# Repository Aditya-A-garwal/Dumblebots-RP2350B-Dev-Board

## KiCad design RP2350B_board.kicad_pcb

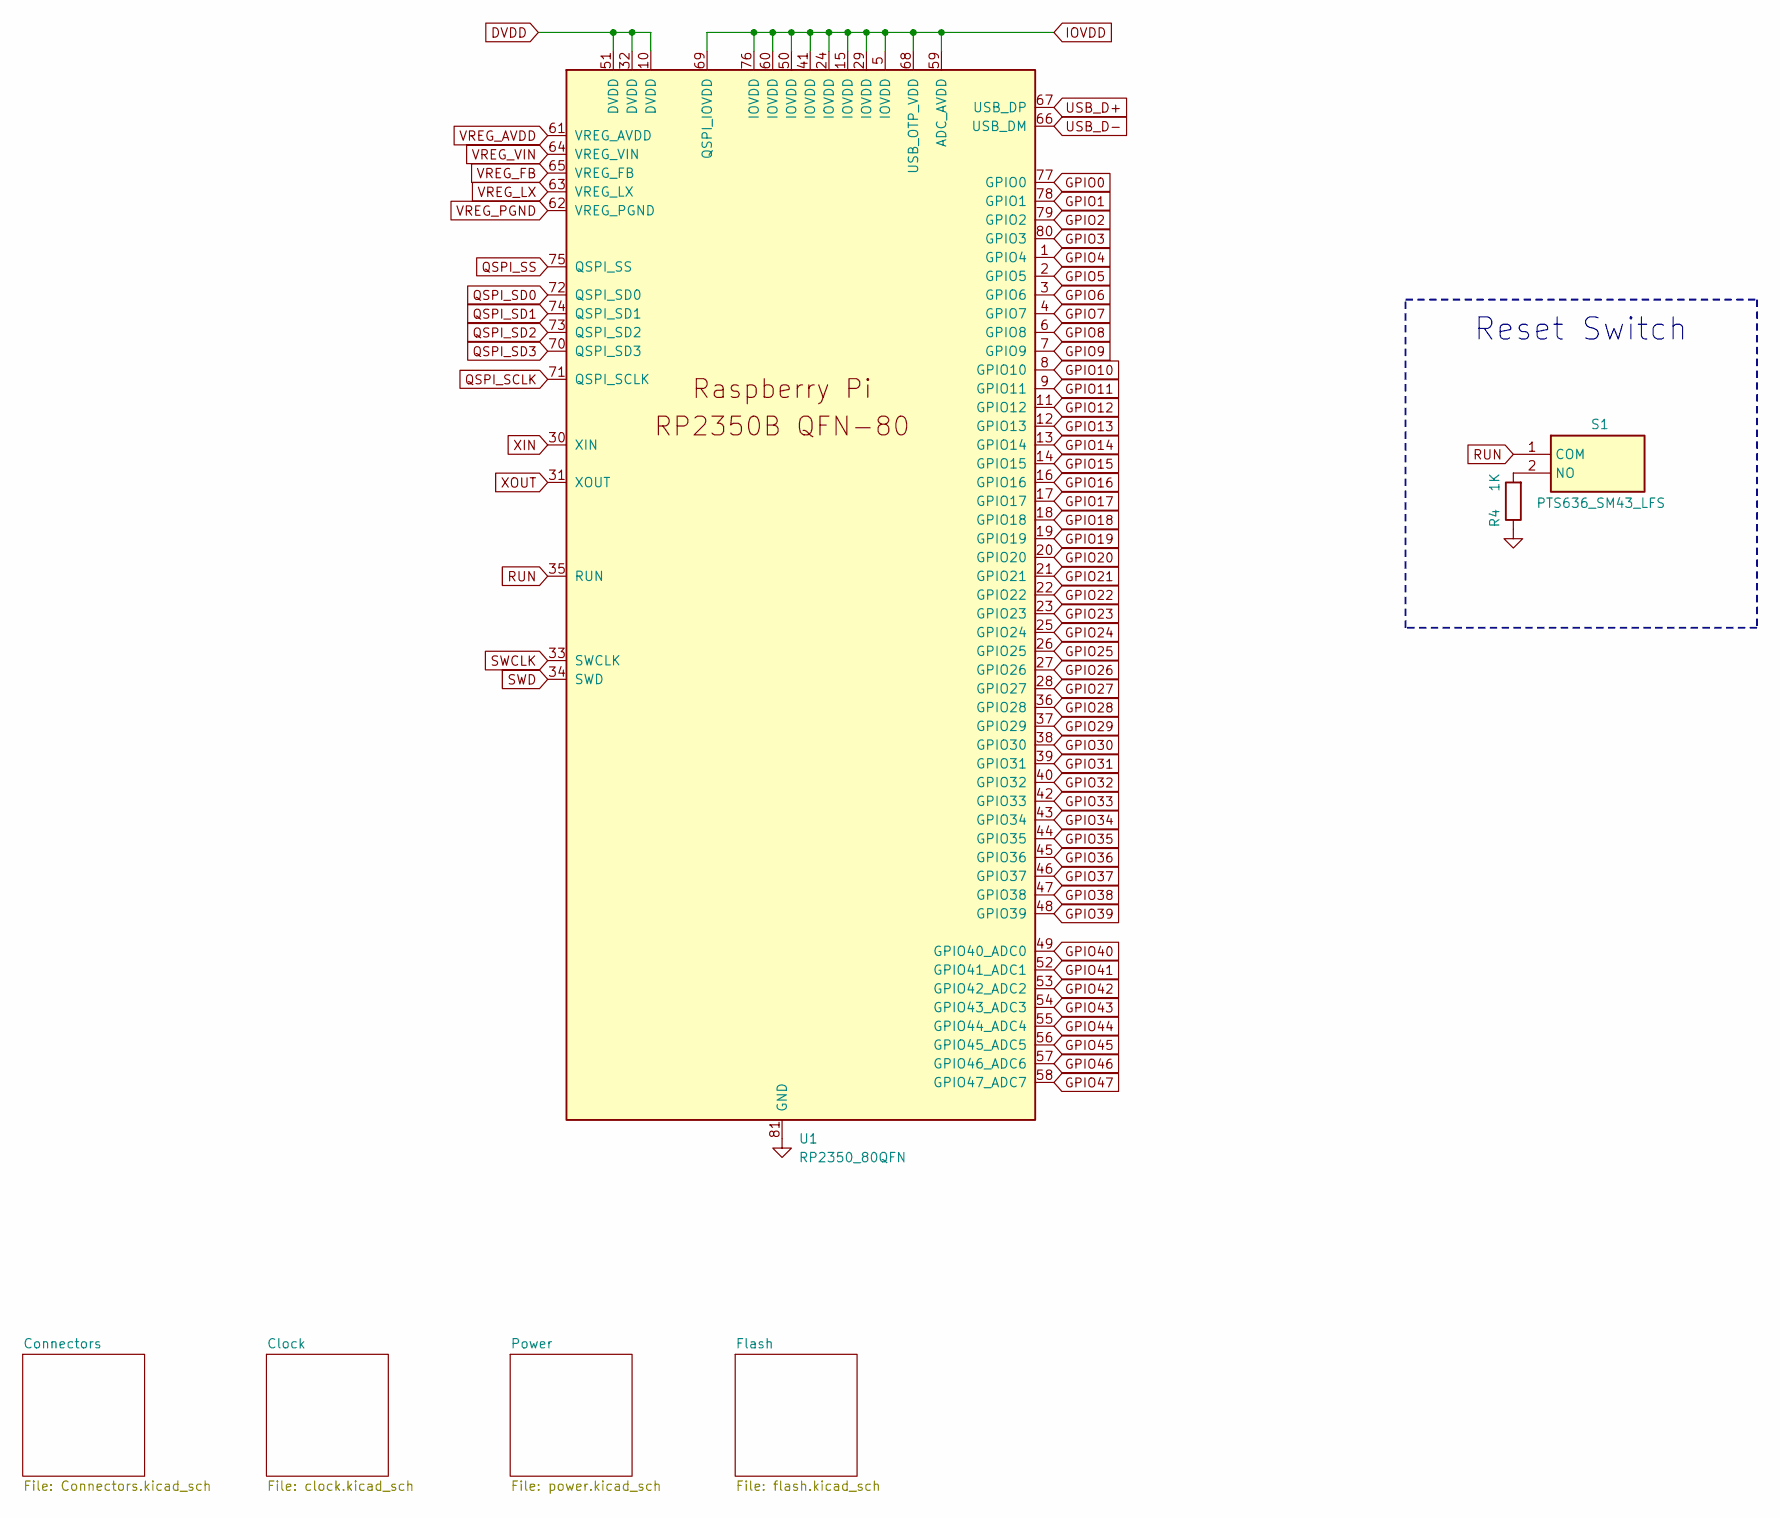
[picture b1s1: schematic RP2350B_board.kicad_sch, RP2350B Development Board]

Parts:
R4: 1K; R_0402_1005Metric
S1: PTS636_SM43_LFS; PTS636SM43LFS; Mouser Part Number 611-PTS636SM43LFS
U1: RP2350_80QFN; RP2350-QFN-80-1EP_10x10_P0.4mm_EP3.4x3.4mm_ThermalVias

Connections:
DVDD: U1.10 (DVDD), U1.32 (DVDD), U1.51 (DVDD), U1.65 (VREG_FB); also elsewhere on the board
GPIO0: U1.75 (QSPI_SS), U1.77 (GPIO0); also elsewhere on the board
GPIO1: U1.78 (GPIO1); also elsewhere on the board
GPIO2: U1.79 (GPIO2); also elsewhere on the board
GPIO3: U1.80 (GPIO3); also elsewhere on the board
GPIO4: U1.1 (GPIO4); also elsewhere on the board
GPIO5: U1.2 (GPIO5); also elsewhere on the board
GPIO6: U1.3 (GPIO6); also elsewhere on the board
GPIO7: U1.4 (GPIO7); also elsewhere on the board
GPIO8: U1.6 (GPIO8); also elsewhere on the board
GPIO9: U1.7 (GPIO9); also elsewhere on the board
GPIO10: U1.8 (GPIO10); also elsewhere on the board
GPIO11: U1.9 (GPIO11); also elsewhere on the board
GPIO12: U1.11 (GPIO12); also elsewhere on the board
GPIO13: U1.12 (GPIO13); also elsewhere on the board
GPIO14: U1.13 (GPIO14); also elsewhere on the board
GPIO15: U1.14 (GPIO15); also elsewhere on the board
GPIO16: U1.16 (GPIO16); also elsewhere on the board
GPIO17: U1.17 (GPIO17); also elsewhere on the board
GPIO18: U1.18 (GPIO18); also elsewhere on the board
GPIO19: U1.19 (GPIO19); also elsewhere on the board
GPIO20: U1.20 (GPIO20); also elsewhere on the board
GPIO21: U1.21 (GPIO21); also elsewhere on the board
GPIO22: U1.22 (GPIO22); also elsewhere on the board
GPIO23: U1.23 (GPIO23); also elsewhere on the board
GPIO24: U1.25 (GPIO24); also elsewhere on the board
GPIO25: U1.26 (GPIO25); also elsewhere on the board
GPIO26: U1.27 (GPIO26); also elsewhere on the board
GPIO27: U1.28 (GPIO27); also elsewhere on the board
GPIO28: U1.36 (GPIO28); also elsewhere on the board
GPIO29: U1.37 (GPIO29); also elsewhere on the board
GPIO30: U1.38 (GPIO30); also elsewhere on the board
GPIO31: U1.39 (GPIO31); also elsewhere on the board
GPIO32: U1.40 (GPIO32); also elsewhere on the board
GPIO33: U1.42 (GPIO33); also elsewhere on the board
GPIO34: U1.43 (GPIO34); also elsewhere on the board
GPIO35: U1.44 (GPIO35); also elsewhere on the board
GPIO36: U1.45 (GPIO36); also elsewhere on the board
GPIO37: U1.46 (GPIO37); also elsewhere on the board
GPIO38: U1.47 (GPIO38); also elsewhere on the board
GPIO39: U1.48 (GPIO39); also elsewhere on the board
GPIO40: U1.49 (GPIO40_ADC0); also elsewhere on the board
GPIO41: U1.52 (GPIO41_ADC1); also elsewhere on the board
GPIO42: U1.53 (GPIO42_ADC2); also elsewhere on the board
GPIO43: U1.54 (GPIO43_ADC3); also elsewhere on the board
GPIO44: U1.55 (GPIO44_ADC4); also elsewhere on the board
GPIO45: U1.56 (GPIO45_ADC5); also elsewhere on the board
GPIO46: U1.57 (GPIO46_ADC6); also elsewhere on the board
GPIO47: U1.58 (GPIO47_ADC7); also elsewhere on the board
IOVDD: U1.5 (IOVDD), U1.15 (IOVDD), U1.24 (IOVDD), U1.29 (IOVDD), U1.41 (IOVDD), U1.50 (IOVDD), U1.59 (ADC_AVDD), U1.60 (IOVDD), U1.64 (VREG_VIN), U1.68 (USB_OTP_VDD), U1.69 (QSPI_IOVDD), U1.76 (IOVDD); also elsewhere on the board
unnamed: R4.2, S1.2 (NO)
QSPI_SCLK: U1.71 (QSPI_SCLK); also elsewhere on the board
QSPI_SD0: U1.72 (QSPI_SD0); also elsewhere on the board
QSPI_SD1: U1.74 (QSPI_SD1); also elsewhere on the board
QSPI_SD2: U1.73 (QSPI_SD2); also elsewhere on the board
QSPI_SD3: U1.70 (QSPI_SD3); also elsewhere on the board
RUN: S1.1 (COM), U1.35 (RUN)
SWCLK: U1.33 (SWCLK)
SWD: U1.34 (SWD)
USB_D+: U1.67 (USB_DP); also elsewhere on the board
USB_D-: U1.66 (USB_DM); also elsewhere on the board
VREG_AVDD: U1.61 (VREG_AVDD); also elsewhere on the board
VREG_LX: U1.63 (VREG_LX); also elsewhere on the board
VREG_PGND: R4.1, U1.62 (VREG_PGND), U1.81 (GND); also elsewhere on the board
XIN: U1.30 (XIN); also elsewhere on the board
XOUT: U1.31 (XOUT); also elsewhere on the board

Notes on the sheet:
Reset Switch

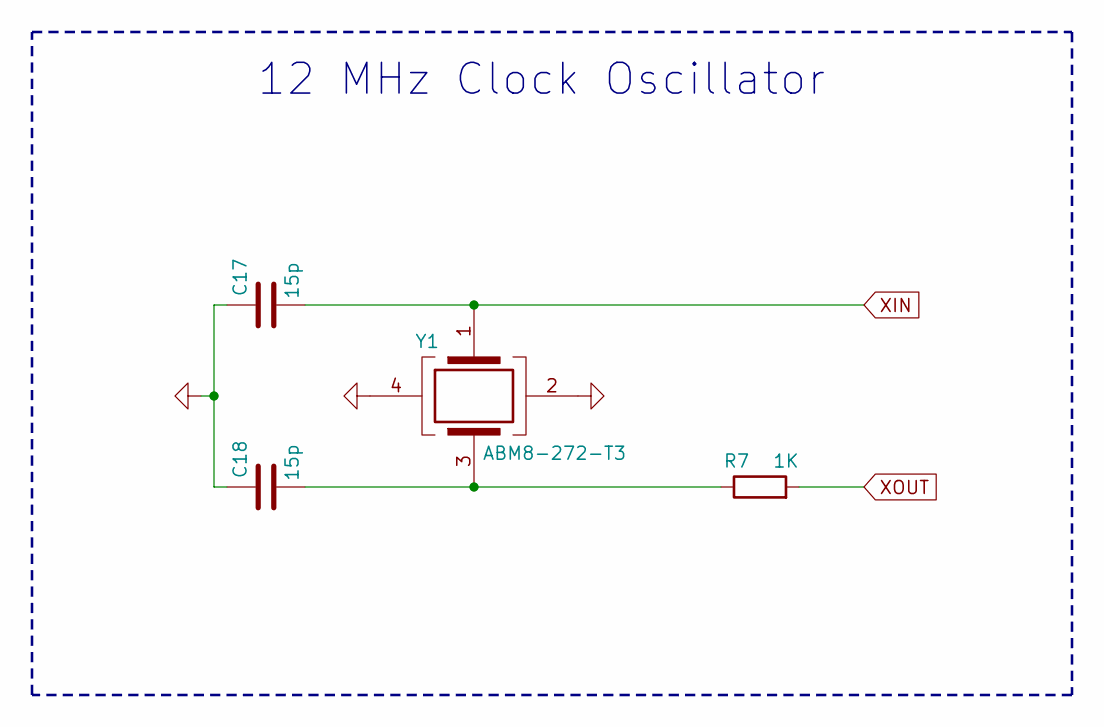
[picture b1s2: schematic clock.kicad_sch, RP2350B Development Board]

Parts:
C17, C18: 15p; C_0402_1005Metric
R7: 1K; R_0402_1005Metric
Y1: ABM8-272-T3; ABM8272T3; Mouser Part Number 815-ABM8-272-T3

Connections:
unnamed: C18.2, R7.1, Y1.3
VREG_PGND: C17.1, C18.1, Y1.2, Y1.4; also elsewhere on the board
XIN: C17.2, Y1.1; also elsewhere on the board
XOUT: R7.2; also elsewhere on the board

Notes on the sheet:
12 MHz Clock Oscillator

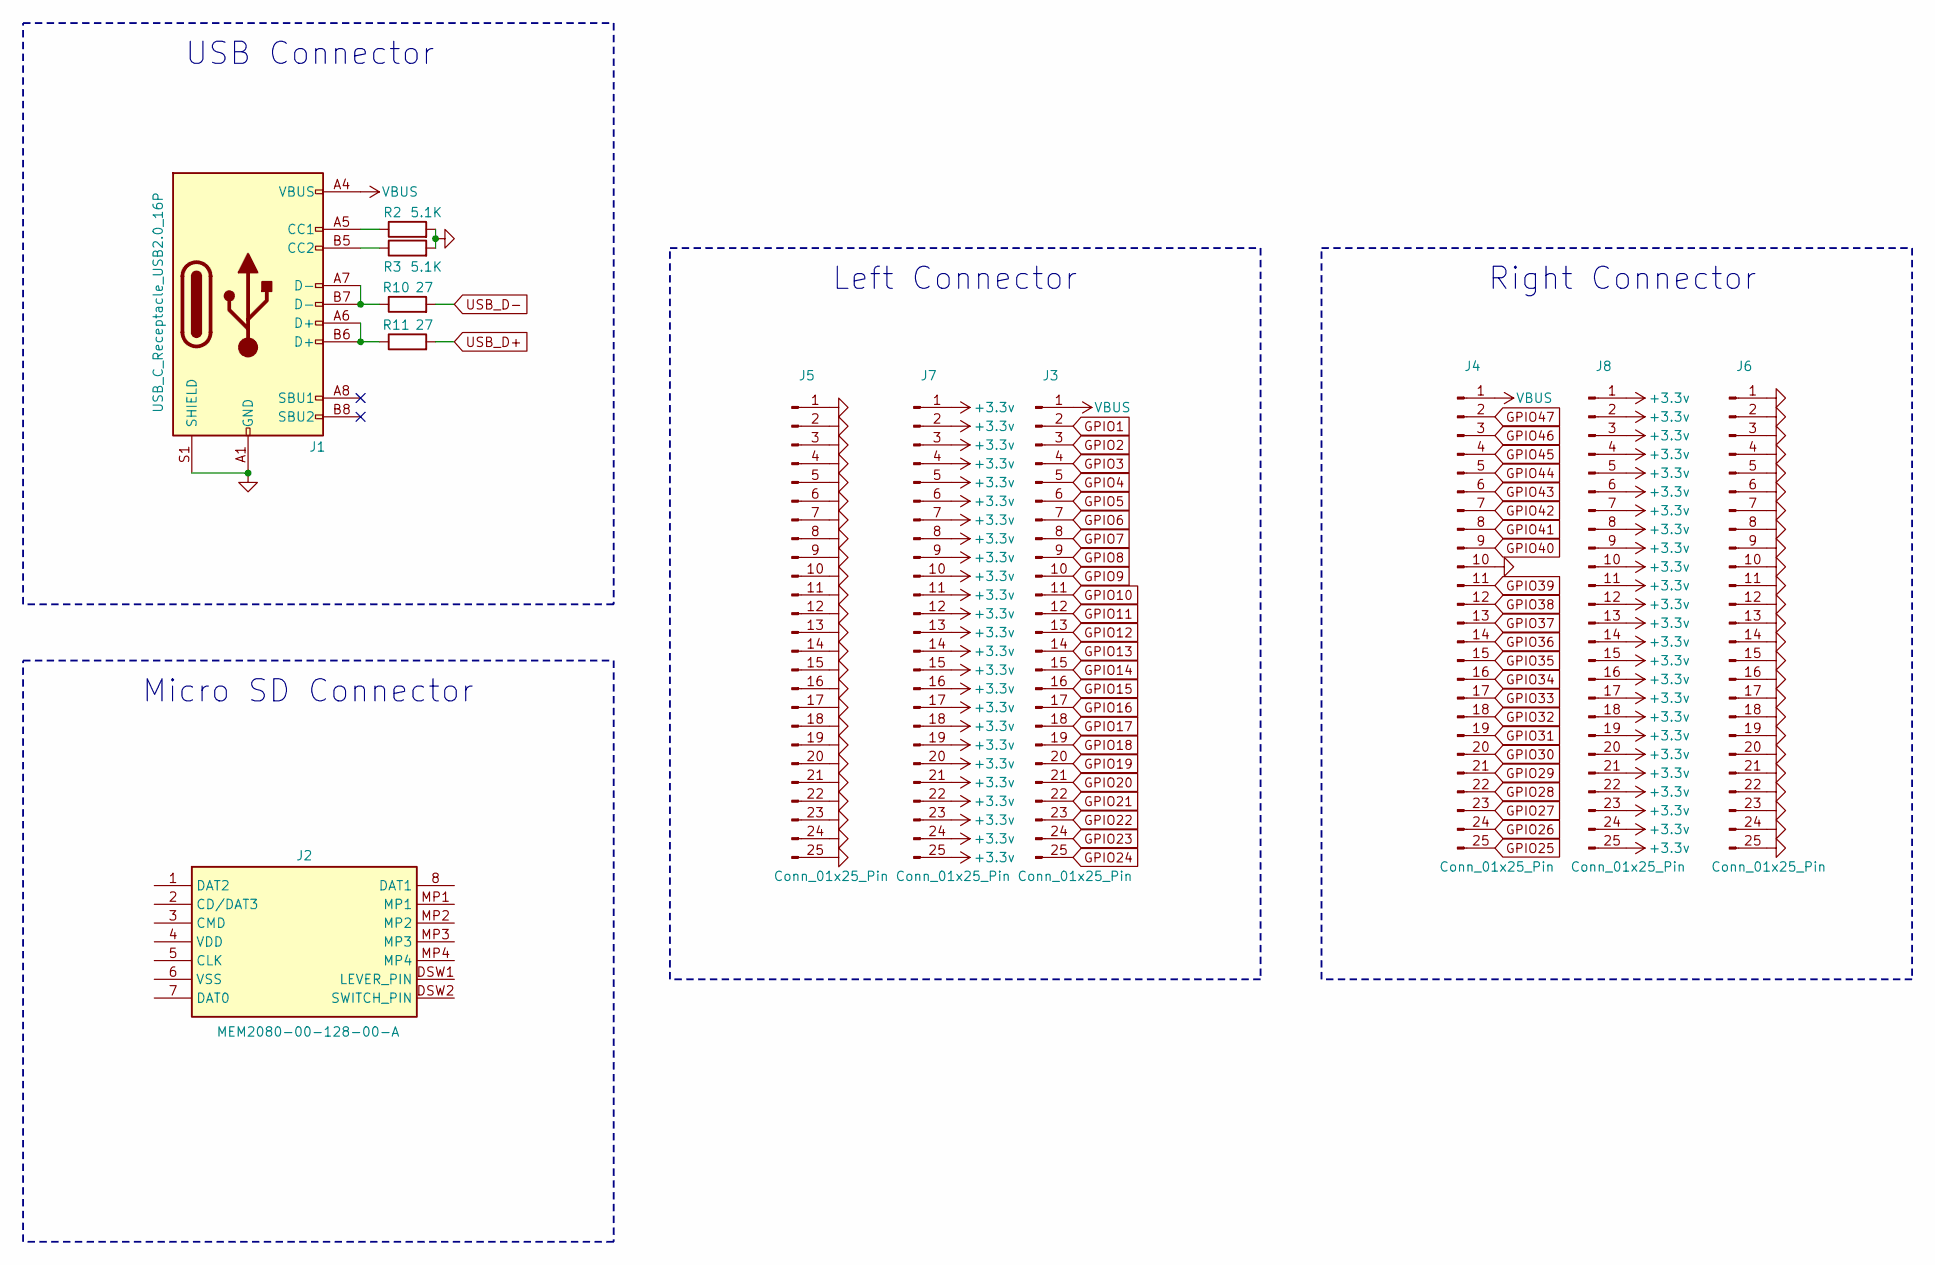
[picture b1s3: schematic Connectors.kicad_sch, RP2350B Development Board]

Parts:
J1: USB_C_Receptacle_USB2.0_16P; USB_C_Receptacle_GCT_USB4105-xx-A_16P_TopMnt_Horizontal
J2: MEM2080-00-128-00-A; MEM20800012800A; Mouser Part Number 640-MEM2080-0012800A
J3, J4, J5, J6, J7, J8: Conn_01x25_Pin; PinHeader_1x25_P2.54mm_Vertical
R2, R3: 5.1K; R_0402_1005Metric
R10, R11: 27; R_0402_1005Metric

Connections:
GPIO1: J3.2; also elsewhere on the board
GPIO2: J3.3; also elsewhere on the board
GPIO3: J3.4; also elsewhere on the board
GPIO4: J3.5; also elsewhere on the board
GPIO5: J3.6; also elsewhere on the board
GPIO6: J3.7; also elsewhere on the board
GPIO7: J3.8; also elsewhere on the board
GPIO8: J3.9; also elsewhere on the board
GPIO9: J3.10; also elsewhere on the board
GPIO10: J3.11; also elsewhere on the board
GPIO11: J3.12; also elsewhere on the board
GPIO12: J3.13; also elsewhere on the board
GPIO13: J3.14; also elsewhere on the board
GPIO14: J3.15; also elsewhere on the board
GPIO15: J3.16; also elsewhere on the board
GPIO16: J3.17; also elsewhere on the board
GPIO17: J3.18; also elsewhere on the board
GPIO18: J3.19; also elsewhere on the board
GPIO19: J3.20; also elsewhere on the board
GPIO20: J3.21; also elsewhere on the board
GPIO21: J3.22; also elsewhere on the board
GPIO22: J3.23; also elsewhere on the board
GPIO23: J3.24; also elsewhere on the board
GPIO24: J3.25; also elsewhere on the board
GPIO25: J4.25; also elsewhere on the board
GPIO26: J4.24; also elsewhere on the board
GPIO27: J4.23; also elsewhere on the board
GPIO28: J4.22; also elsewhere on the board
GPIO29: J4.21; also elsewhere on the board
GPIO30: J4.20; also elsewhere on the board
GPIO31: J4.19; also elsewhere on the board
GPIO32: J4.18; also elsewhere on the board
GPIO33: J4.17; also elsewhere on the board
GPIO34: J4.16; also elsewhere on the board
GPIO35: J4.15; also elsewhere on the board
GPIO36: J4.14; also elsewhere on the board
GPIO37: J4.13; also elsewhere on the board
GPIO38: J4.12; also elsewhere on the board
GPIO39: J4.11; also elsewhere on the board
GPIO40: J4.9; also elsewhere on the board
GPIO41: J4.8; also elsewhere on the board
GPIO42: J4.7; also elsewhere on the board
GPIO43: J4.6; also elsewhere on the board
GPIO44: J4.5; also elsewhere on the board
GPIO45: J4.4; also elsewhere on the board
GPIO46: J4.3; also elsewhere on the board
GPIO47: J4.2; also elsewhere on the board
IOVDD: J7.1, J7.2, J7.3, J7.4, J7.5, J7.6, J7.7, J7.8, J7.9, J7.10, J7.11, J7.12, J7.13, J7.14, J7.15, J7.16, J7.17, J7.18, J7.19, J7.20, J7.21, J7.22, J7.23, J7.24, J7.25, J8.1, J8.2, J8.3, J8.4, J8.5, J8.6, J8.7, J8.8, J8.9, J8.10, J8.11, J8.12, J8.13, J8.14, J8.15, J8.16, J8.17, J8.18, J8.19, J8.20, J8.21, J8.22, J8.23, J8.24, J8.25; also elsewhere on the board
unnamed: J1.A5 (CC1), R2.1
unnamed: J1.B5 (CC2), R3.1
unnamed: J1.A6 (D+), J1.B6 (D+), R11.1
unnamed: J1.A7 (D-), J1.B7 (D-), R10.1
USB_D+: R11.2; also elsewhere on the board
USB_D-: R10.2; also elsewhere on the board
VBUS: J1.A4 (VBUS), J1.A9 (VBUS), J1.B4 (VBUS), J1.B9 (VBUS), J3.1, J4.1; also elsewhere on the board
VREG_PGND: J1.A1 (GND), J1.A12 (GND), J1.B1 (GND), J1.B12 (GND), J1.S1 (SHIELD), J4.10, J5.1, J5.2, J5.3, J5.4, J5.5, J5.6, J5.7, J5.8, J5.9, J5.10, J5.11, J5.12, J5.13, J5.14, J5.15, J5.16, J5.17, J5.18, J5.19, J5.20, J5.21, J5.22, J5.23, J5.24, J5.25, J6.1, J6.2, J6.3, J6.4, J6.5, J6.6, J6.7, J6.8, J6.9, J6.10, J6.11, J6.12, J6.13, J6.14, J6.15, J6.16, J6.17, J6.18, J6.19, J6.20, J6.21, J6.22, J6.23, J6.24, J6.25, R2.2, R3.2; also elsewhere on the board

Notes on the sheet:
USB Connector
Left Connector
Right Connector
Micro SD Connector

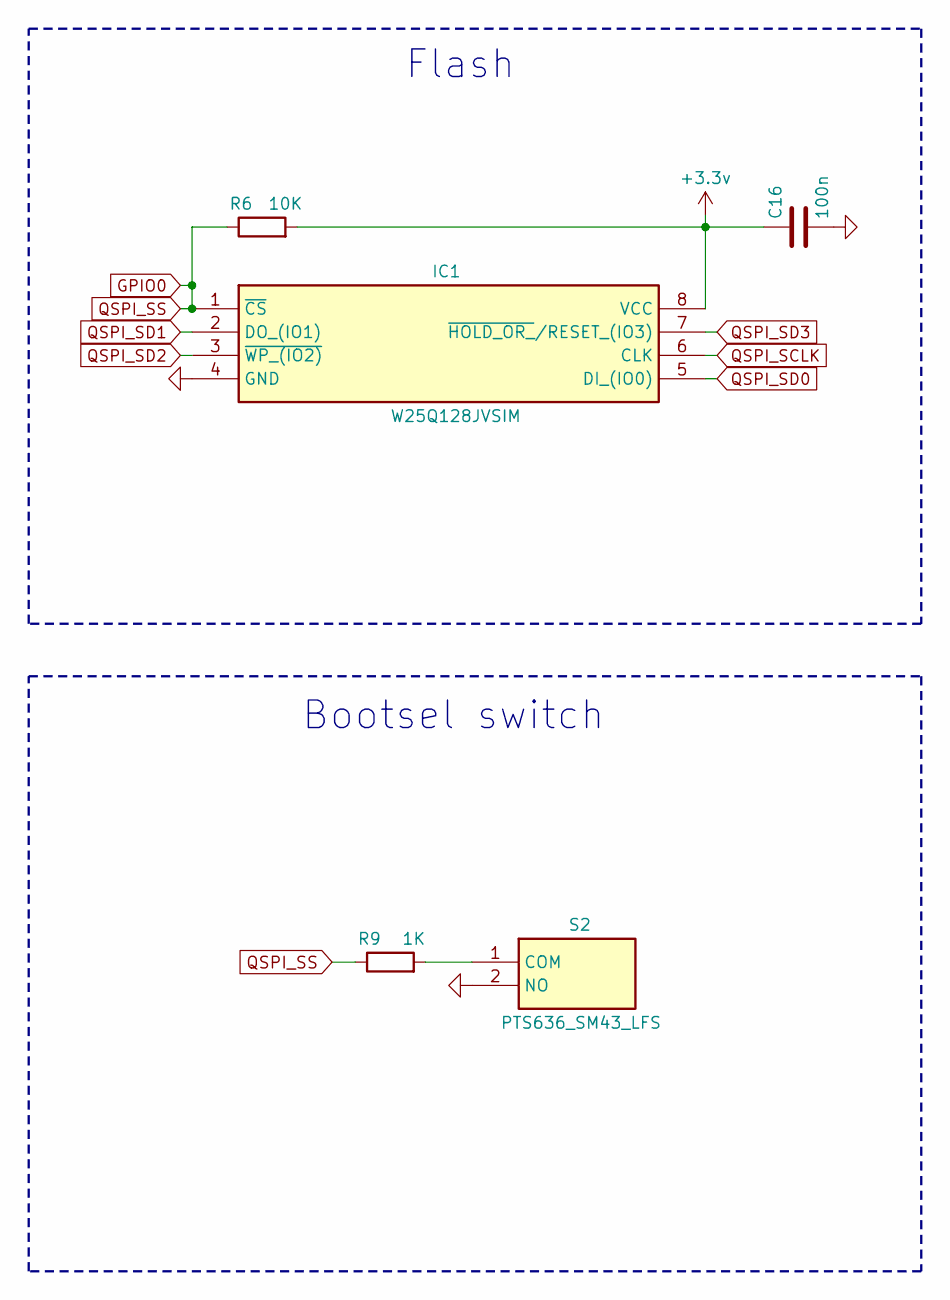
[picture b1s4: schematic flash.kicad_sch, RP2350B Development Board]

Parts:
C16: 100n; C_0402_1005Metric
IC1: W25Q128JVSIM; SOIC127P790X216-8N; Mouser Part Number 454-W25Q128JVSIM
R6: 10K; R_0402_1005Metric
R9: 1K; R_0402_1005Metric
S2: PTS636_SM43_LFS; PTS636SM43LFS; Mouser Part Number 611-PTS636SM43LFS

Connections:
GPIO0: IC1.1 (~CS), R6.1, R9.1; also elsewhere on the board
IOVDD: C16.1, IC1.8 (VCC), R6.2; also elsewhere on the board
unnamed: R9.2, S2.1 (COM)
QSPI_SCLK: IC1.6 (CLK); also elsewhere on the board
QSPI_SD0: IC1.5 (DI_(IO0)); also elsewhere on the board
QSPI_SD1: IC1.2 (DO_(IO1)); also elsewhere on the board
QSPI_SD2: IC1.3 (~WP_(IO2)); also elsewhere on the board
QSPI_SD3: IC1.7 (~HOLD_OR_/RESET_(IO3)); also elsewhere on the board
VREG_PGND: C16.2, IC1.4 (GND), S2.2 (NO); also elsewhere on the board

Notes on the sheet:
Flash
Bootsel switch

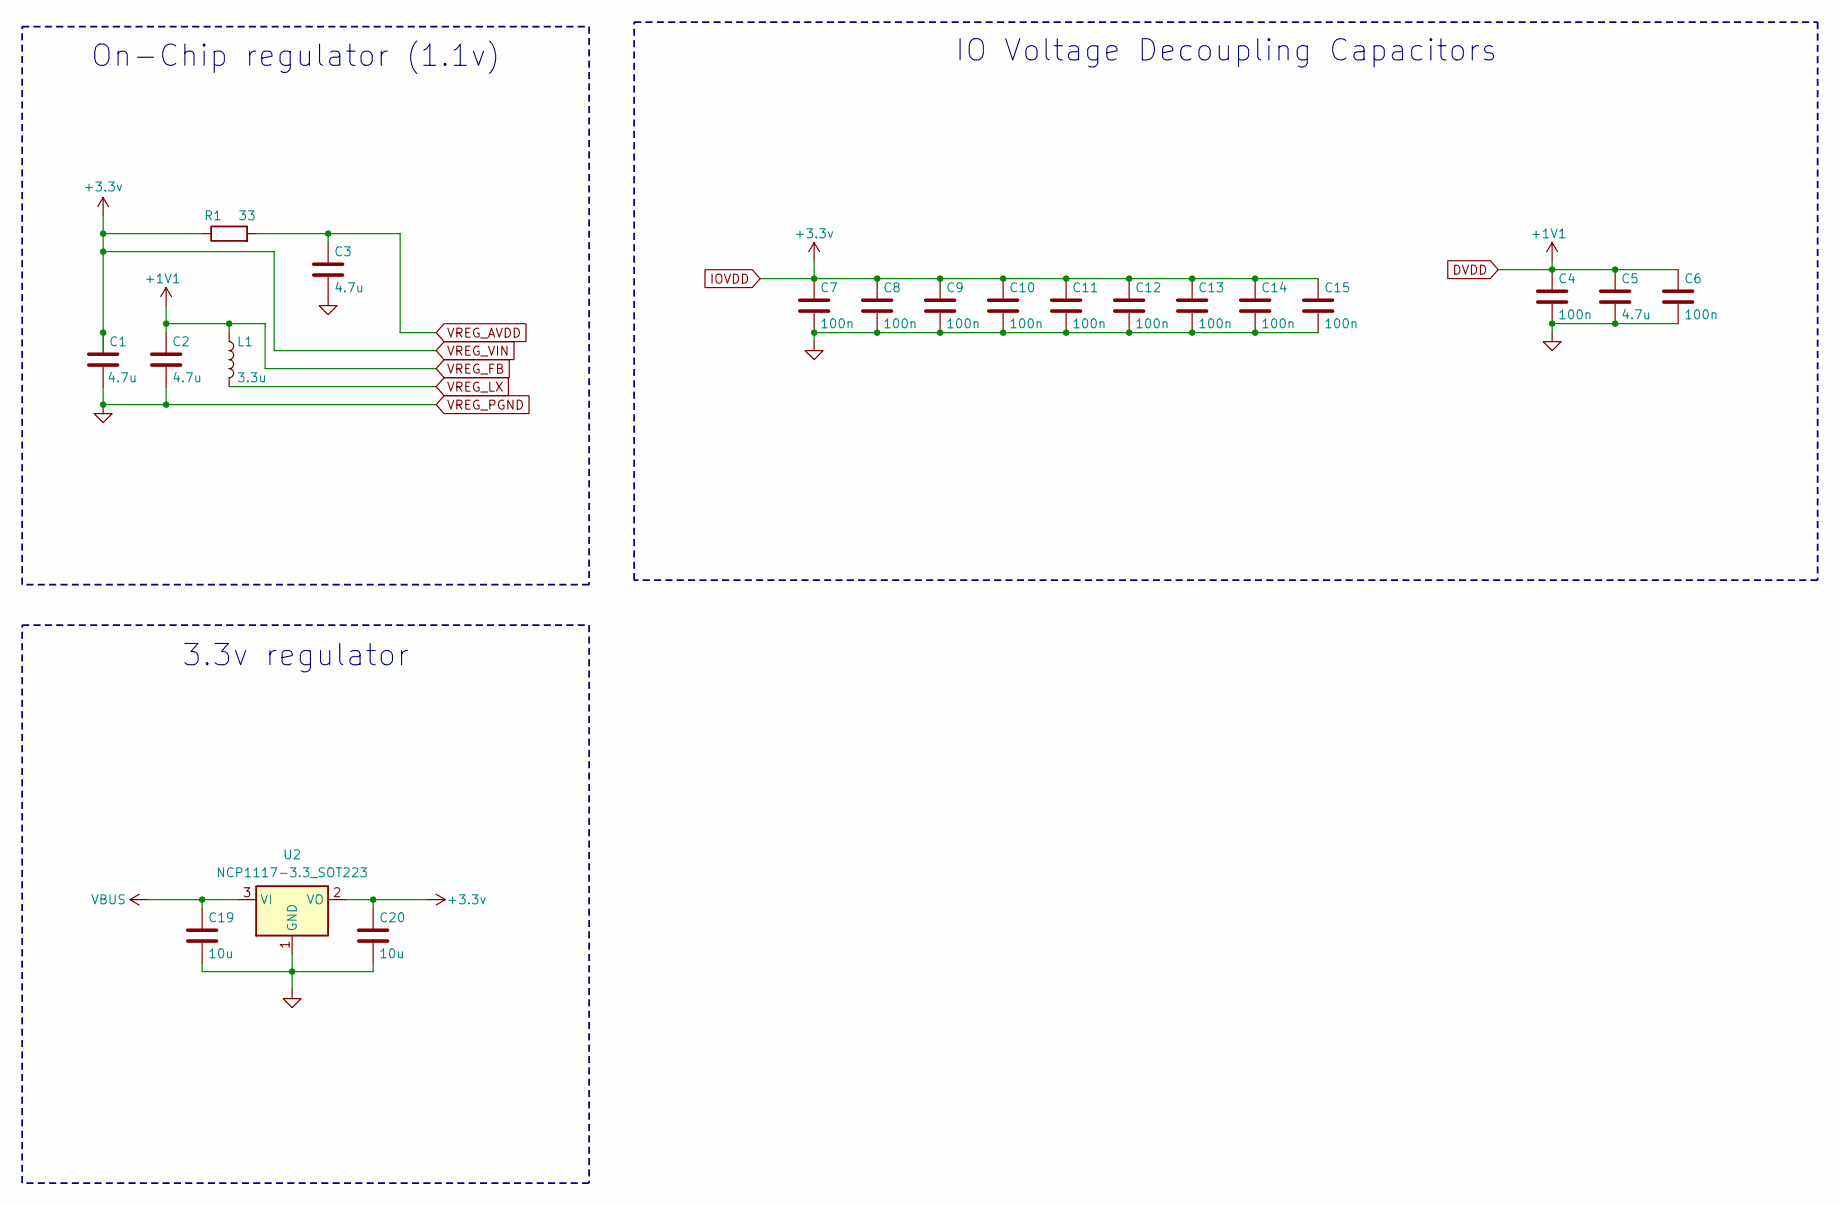
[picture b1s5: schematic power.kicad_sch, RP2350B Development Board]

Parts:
C1, C2, C3, C5: 4.7u; C_0402_1005Metric
C4, C6, C7, C8, C9, C10, C11, C12, C13, C14, C15: 100n; C_0402_1005Metric
C19, C20: 10u; C_0402_1005Metric
L1: 3.3u; L_0805_2012Metric
R1: 33; R_0402_1005Metric
U2: NCP1117-3.3_SOT223; SOT-223-3_TabPin2

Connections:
DVDD: C2.1, C4.1, C5.1, C6.1, L1.1; also elsewhere on the board
IOVDD: C1.1, C7.1, C8.1, C9.1, C10.1, C11.1, C12.1, C13.1, C14.1, C15.1, C20.1, R1.1, U2.2 (VO); also elsewhere on the board
VBUS: C19.1, U2.3 (VI); also elsewhere on the board
VREG_AVDD: C3.1, R1.2; also elsewhere on the board
VREG_LX: L1.2; also elsewhere on the board
VREG_PGND: C1.2, C2.2, C3.2, C4.2, C5.2, C6.2, C7.2, C8.2, C9.2, C10.2, C11.2, C12.2, C13.2, C14.2, C15.2, C19.2, C20.2, U2.1 (GND); also elsewhere on the board

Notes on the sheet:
On-Chip regulator (1.1v)
IO Voltage Decoupling Capacitors
3.3v regulator

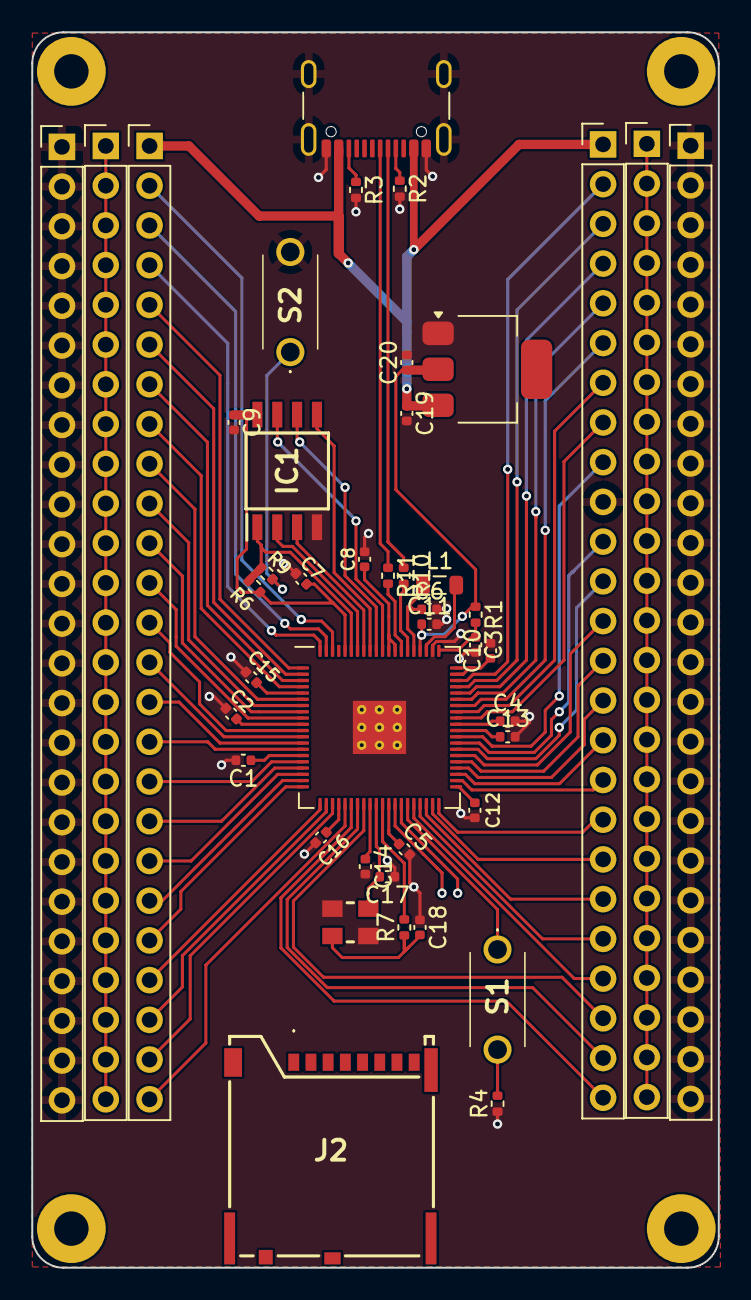
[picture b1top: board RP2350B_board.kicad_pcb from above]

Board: 2 copper layers, 43.9 x 79.0 mm, 44 parts (0 on the bottom side), 71 nets.

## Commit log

2024-10-18 feat: add initial design
2024-10-24 refactor: start new layout
2024-10-24 feat: complete all features except SD Card reader
2024-10-24 fix: remove copper area from under inductor
2024-10-24 fix: add seperate via for Cfilter
